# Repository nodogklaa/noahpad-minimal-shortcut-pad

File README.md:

# noahpad

My friend told me about this event abit ago and I finally got it done. This is the first time I have tried something like this and I think it turned out alright. 
Since this is my first time and it was a bit rushed (due to tests coming up) I doubt everything will work correctly.
Also my firmware doesnt support the OLED at this momment. This mainly because I forgot and I dont currently have the time to fix it. Once I get everything else working I will add it in, hopefully its a simple fix.

It is a 11 key macropad with an encoder and Oled display and uses QMK firmware.

**Specifications**
BOM
-11x Cherry MX Switches
-1x XIAO RP2040
-11x Blank DSA Keycaps
-4x M3x16 Bolt
-4x M3 Heatset
-1x EC11 Rotary encoders
-1x 0.91 inch OLED display
-1 Case (2 3d printed parts)
-12x through-hole 1N4148 Diodes

**CAD** 

The case fits together 4 M3 bolt inserts in the case. 
It has 2 seperate parts.
For me I found this stage the most fun.
Made in OnShape

**PCB** 

This is my PCB, it was made in KiCad.

PCB:

Schematic:

**FIRMWARE**

I used qmk firmware. This stage took me the longest by far.
As I mentioned before I forgot to include the oled in it, but I plan to fix it once school calms down again.

**More CAD Images**

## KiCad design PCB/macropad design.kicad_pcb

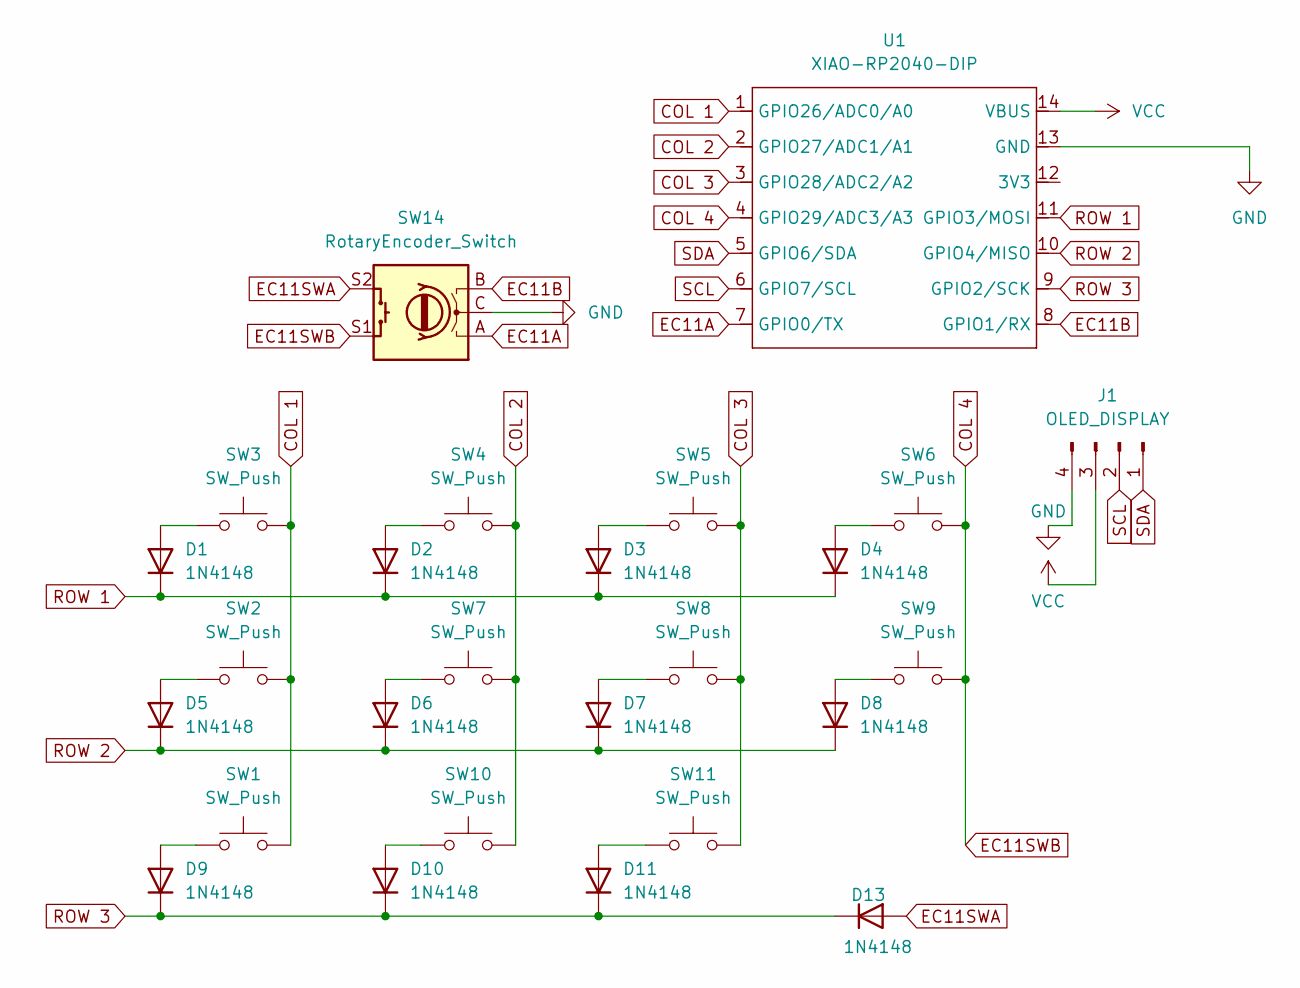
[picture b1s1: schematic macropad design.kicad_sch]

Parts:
D1, D2, D3, D4, D5, D6, D7, D8, D9, D10, D11, D13: 1N4148; D_DO-35_SOD27_P7.62mm_Horizontal
J1: OLED_DISPLAY; SSD1306-0.91-OLED-4pin-128x32 (1)
SW1, SW2, SW3, SW4, SW5, SW6, SW7, SW8, SW9, SW10, SW11: SW_Push; SW_Cherry_MX_1.00u_PCB
SW14: RotaryEncoder_Switch; RotaryEncoder_Alps_EC11E-Switch_Vertical_H20mm
U1: XIAO-RP2040-DIP

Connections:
COL 1: SW1.2, SW2.2, SW3.2, U1.1 (GPIO26/ADC0/A0)
COL 2: SW4.2, SW7.2, SW10.2, U1.2 (GPIO27/ADC1/A1)
COL 3: SW5.2, SW8.2, SW11.2, U1.3 (GPIO28/ADC2/A2)
COL 4: SW6.2, SW9.2, SW14.S1, U1.4 (GPIO29/ADC3/A3)
EC11A: SW14.A, U1.7 (GPIO0/TX)
EC11B: SW14.B, U1.8 (GPIO1/RX)
EC11SWA: D13.2 (A), SW14.S2
GND: J1.4, SW14.C, U1.13 (GND)
unnamed: D1.2 (A), SW3.1
unnamed: D2.2 (A), SW4.1
unnamed: D3.2 (A), SW5.1
unnamed: D4.2 (A), SW6.1
unnamed: D5.2 (A), SW2.1
unnamed: D6.2 (A), SW7.1
unnamed: D7.2 (A), SW8.1
unnamed: D8.2 (A), SW9.1
unnamed: D9.2 (A), SW1.1
unnamed: D10.2 (A), SW10.1
unnamed: D11.2 (A), SW11.1
ROW 1: D1.1 (K), D2.1 (K), D3.1 (K), D4.1 (K), U1.11 (GPIO3/MOSI)
ROW 2: D5.1 (K), D6.1 (K), D7.1 (K), D8.1 (K), U1.10 (GPIO4/MISO)
ROW 3: D9.1 (K), D10.1 (K), D11.1 (K), D13.1 (K), U1.9 (GPIO2/SCK)
SCL: J1.2, U1.6 (GPIO7/SCL)
SDA: J1.1, U1.5 (GPIO6/SDA)
VCC: J1.3, U1.14 (VBUS)

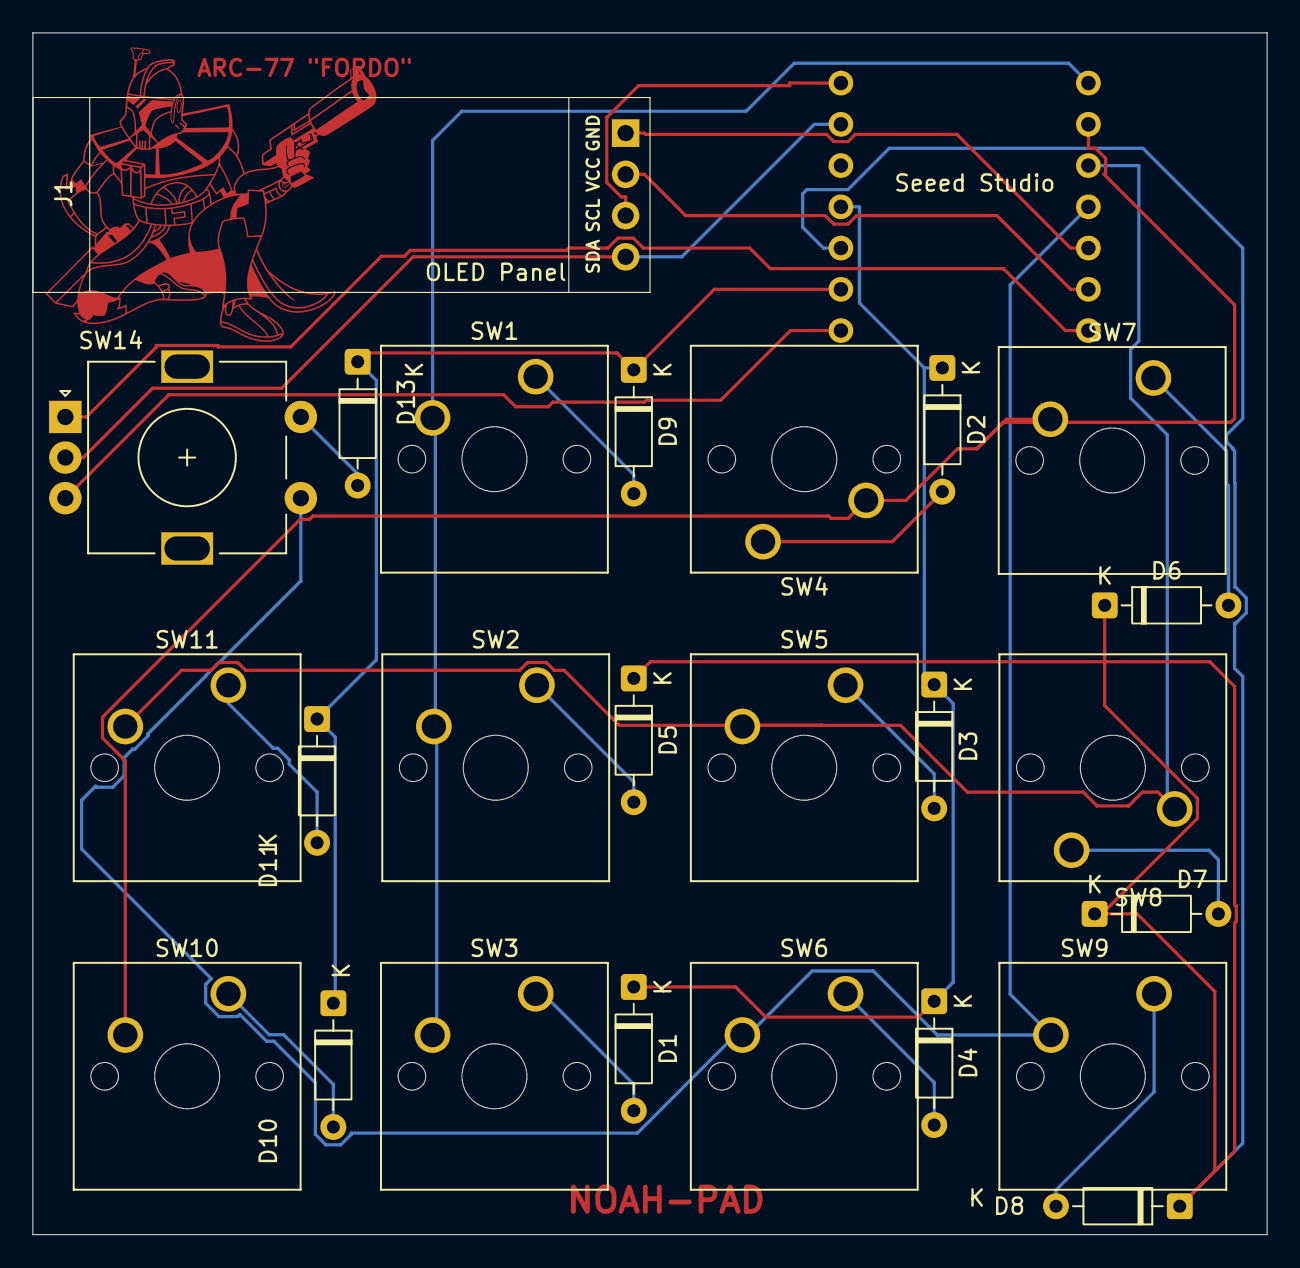
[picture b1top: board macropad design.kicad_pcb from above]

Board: 2 copper layers, 76.0 x 74.0 mm, 26 parts (1 on the bottom side), 25 nets.

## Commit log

2026-03-28 Create CAD
2026-03-28 Create temp
